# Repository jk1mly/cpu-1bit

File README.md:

# cpu-1bit
MC14500 1bit CPU

MC14500Bを使って実験を行うための基板と、プログラムをEPROMの代わりにPICに入れるソフト
MC14500Bのソフトはprogcd.hに記述
ニーモニックどはopcode.hに定義
main.cはアドレスに従ってデータを出すのみ
PICでの遅延が大きいので16F1938を32Mで動かしている
（あくまでもMC14500Bを使うのが目的）

ICソケットに実装する前に電源のショートなど確認する
電池を入れて電源を供給、PWRのLEDで電源極性を確認
電源を切ってICを実装、向きがバラバラなので注意
J3はS；スロー側に設定、ジャンパポストはオープンで良い
IN(J10)とOUT(J4)のb1、INのb2をGND(J6 3)、b3を+V(J6 1)に接続
（テスト用のプログラムだけならb3のみで良い、接続はプログラムに依存）
電源を入れて異常がなければPICkitを接続
（PICkitからは電源を供給しない・デフォルト）
PICにプログラムしたらPICkitを外す
RUNのスイッチを押すとプルグラムが動く

（PICで動かすなら3Vか4.5V）
SW4を押すとCPUがリセットされる
同時にROMアドレスの上位が1になりEPROMの書き込んでない領域になる
これによりCPUにはFが入力されるのでFLGFが出てぷrグラムカウンタが0になる
試験用のプログラムはDIPスイッチのNOT, AND, OR, XORをLEDに表示する

改善点
SW4とパラに0.1uFを入れておいた方が良い
（電源ON時にリセット状態で止められる・動かしたいならSW3）
RUNとWRITEのLEDを付けておいた方が良い
データとして0,1、ラッチしたデータを読める入力があった方が良い
（ジャンパするよう基板を作ってあるが、ジャンパポストを設けるべき）
ラッチ4ビットのLEDに入れる抵抗は別回路な方が良い
（外部I/Oで使うための抵抗と兼用になっている）

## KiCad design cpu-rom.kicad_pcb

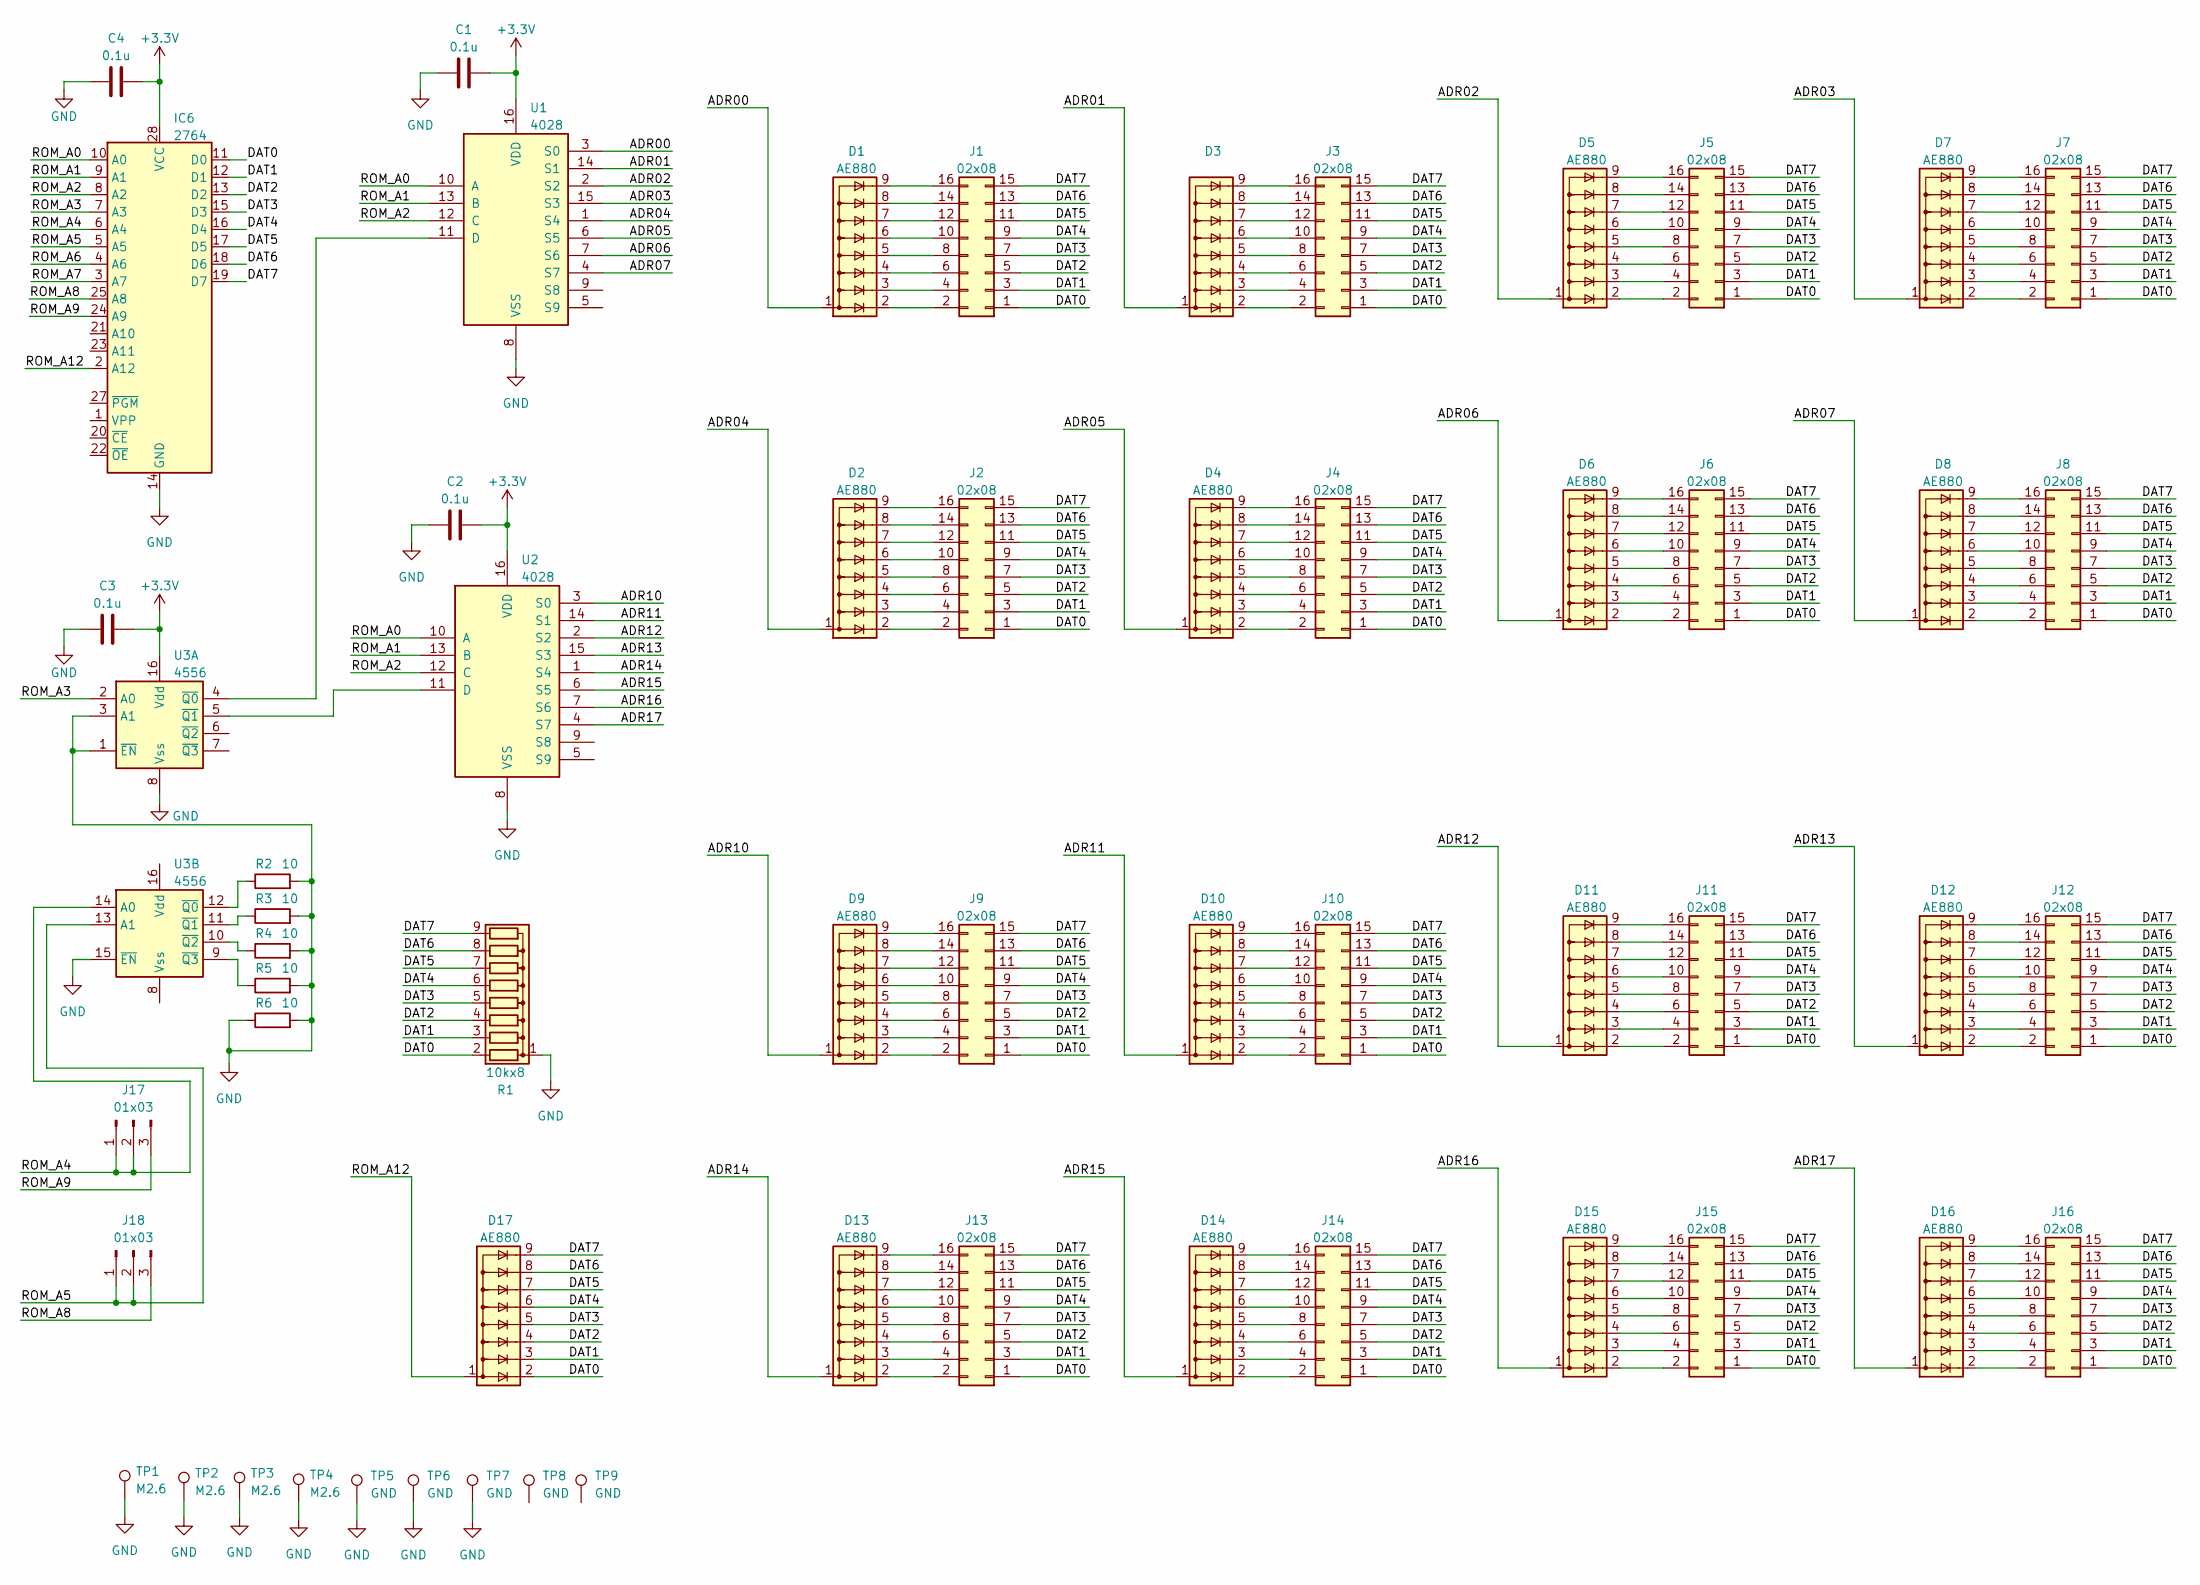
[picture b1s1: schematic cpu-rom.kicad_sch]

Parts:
C1, C2, C3, C4: 0.1u; C_Disc_P2.54mm
D1, D2, D3, D4, D5, D6, D7, D8, D9, D10, D11, D12, D13, D14, D15, D16, D17: AE880; R_Array_SIP9
IC6: 2764; DIP-28_W15.24mm_Socket_mini
J1, J2, J3, J4, J5, J6, J7, J8, J9, J10, J11, J12, J13, J14, J15, J16: 02x08; PinHeader_2x08_P2.54mm_Vertical
J17, J18: 01x03; PinHeader_1x03_P2.54mm_Vertical
R1: 10kx8; R_Array_SIP9
R2, R3, R4, R5, R6: 10; R_Axial_DIN0207_L6.3mm_D2.2mm_P2.54mm_Vertical
TP1, TP2, TP3, TP4: M2.6; TestPoint_Drill3mm
TP5, TP6, TP7, TP8, TP9: GND; TestPoint_2Pads_Pitch2.54mm_Drill0.8mm
U1, U2: 4028; DIP-16_W7.62mm_Socket_mini
U3: 4556; DIP-16_W7.62mm_Socket_mini

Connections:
+3.3V: C1.2, C2.2, C3.2, C4.2, IC6.28 (VCC), U1.16 (VDD), U2.16 (VDD), U3.16 (Vdd)
/ADR00: D1.1 (common), U1.3 (S0)
/ADR01: D3.1 (common), U1.14 (S1)
/ADR02: D5.1 (common), U1.2 (S2)
/ADR03: D7.1 (common), U1.15 (S3)
/ADR04: D2.1 (common), U1.1 (S4)
/ADR05: D4.1 (common), U1.6 (S5)
/ADR06: D6.1 (common), U1.7 (S6)
/ADR07: D8.1 (common), U1.4 (S7)
/ADR10: D9.1 (common), U2.3 (S0)
/ADR11: D10.1 (common), U2.14 (S1)
/ADR12: D11.1 (common), U2.2 (S2)
/ADR13: D12.1 (common), U2.15 (S3)
/ADR14: D13.1 (common), U2.1 (S4)
/ADR15: D14.1 (common), U2.6 (S5)
/ADR16: D15.1 (common), U2.7 (S6)
/ADR17: D16.1 (common), U2.4 (S7)
/DAT0: D17.2 (R1), IC6.11 (D0), J1.1, J2.1, J3.1, J4.1, J5.1, J6.1, J7.1, J8.1, J9.1, J10.1, J11.1, J12.1, J13.1, J14.1, J15.1, J16.1, R1.2 (R1)
/DAT1: D17.3 (R2), IC6.12 (D1), J1.3, J2.3, J3.3, J4.3, J5.3, J6.3, J7.3, J8.3, J9.3, J10.3, J11.3, J12.3, J13.3, J14.3, J15.3, J16.3, R1.3 (R2)
/DAT2: D17.4 (R3), IC6.13 (D2), J1.5, J2.5, J3.5, J4.5, J5.5, J6.5, J7.5, J8.5, J9.5, J10.5, J11.5, J12.5, J13.5, J14.5, J15.5, J16.5, R1.4 (R3)
/DAT3: D17.5 (R4), IC6.15 (D3), J1.7, J2.7, J3.7, J4.7, J5.7, J6.7, J7.7, J8.7, J9.7, J10.7, J11.7, J12.7, J13.7, J14.7, J15.7, J16.7, R1.5 (R4)
/DAT4: D17.6 (R5), IC6.16 (D4), J1.9, J2.9, J3.9, J4.9, J5.9, J6.9, J7.9, J8.9, J9.9, J10.9, J11.9, J12.9, J13.9, J14.9, J15.9, J16.9, R1.6 (R5)
/DAT5: D17.7 (R6), IC6.17 (D5), J1.11, J2.11, J3.11, J4.11, J5.11, J6.11, J7.11, J8.11, J9.11, J10.11, J11.11, J12.11, J13.11, J14.11, J15.11, J16.11, R1.7 (R6)
/DAT6: D17.8 (R7), IC6.18 (D6), J1.13, J2.13, J3.13, J4.13, J5.13, J6.13, J7.13, J8.13, J9.13, J10.13, J11.13, J12.13, J13.13, J14.13, J15.13, J16.13, R1.8 (R7)
/DAT7: D17.9 (R8), IC6.19 (D7), J1.15, J2.15, J3.15, J4.15, J5.15, J6.15, J7.15, J8.15, J9.15, J10.15, J11.15, J12.15, J13.15, J14.15, J15.15, J16.15, R1.9 (R8)
/ROM_A0: IC6.10 (A0), U1.10 (A), U2.10 (A)
/ROM_A1: IC6.9 (A1), U1.13 (B), U2.13 (B)
/ROM_A2: IC6.8 (A2), U1.12 (C), U2.12 (C)
/ROM_A3: IC6.7 (A3), U3.2 (A0)
/ROM_A4: IC6.6 (A4), J17.1, J17.2, U3.14 (A0)
/ROM_A5: IC6.5 (A5), J18.1, J18.2, U3.13 (A1)
/ROM_A6: IC6.4 (A6)
/ROM_A7: IC6.3 (A7)
/ROM_A8: IC6.25 (A8), J18.3
/ROM_A9: IC6.24 (A9), J17.3
/ROM_A12: D17.1 (common), IC6.2 (A12)
GND: C1.1, C2.1, C3.1, C4.1, IC6.14 (GND), R1.1 (common), R2.2, R3.2, R4.2, R5.2, R6.1, R6.2, TP1.1, TP2.1, TP3.1, TP4.1, TP5.1, TP6.1, TP7.1, U1.8 (VSS), U2.8 (VSS), U3.1 (~EN), U3.3 (A1), U3.8 (Vss), U3.15 (~EN)
unnamed: D1.2 (R1), J1.2
unnamed: D1.3 (R2), J1.4
unnamed: D1.4 (R3), J1.6
unnamed: D1.5 (R4), J1.8
unnamed: D1.6 (R5), J1.10
unnamed: D1.7 (R6), J1.12
unnamed: D1.8 (R7), J1.14
unnamed: D1.9 (R8), J1.16
unnamed: D2.2 (R1), J2.2
unnamed: D2.3 (R2), J2.4
unnamed: D2.4 (R3), J2.6
unnamed: D2.5 (R4), J2.8
unnamed: D2.6 (R5), J2.10
unnamed: D2.7 (R6), J2.12
unnamed: D2.8 (R7), J2.14
unnamed: D2.9 (R8), J2.16
unnamed: D3.2 (R1), J3.2
unnamed: D3.3 (R2), J3.4
unnamed: D3.4 (R3), J3.6
unnamed: D3.5 (R4), J3.8
unnamed: D3.6 (R5), J3.10
unnamed: D3.7 (R6), J3.12
unnamed: D3.8 (R7), J3.14
unnamed: D3.9 (R8), J3.16
unnamed: D4.2 (R1), J4.2
unnamed: D4.3 (R2), J4.4
unnamed: D4.4 (R3), J4.6
unnamed: D4.5 (R4), J4.8
unnamed: D4.6 (R5), J4.10
unnamed: D4.7 (R6), J4.12
unnamed: D4.8 (R7), J4.14
unnamed: D4.9 (R8), J4.16
unnamed: D5.2 (R1), J5.2
unnamed: D5.3 (R2), J5.4
unnamed: D5.4 (R3), J5.6
unnamed: D5.5 (R4), J5.8
unnamed: D5.6 (R5), J5.10
unnamed: D5.7 (R6), J5.12
unnamed: D5.8 (R7), J5.14
unnamed: D5.9 (R8), J5.16
unnamed: D6.2 (R1), J6.2
unnamed: D6.3 (R2), J6.4
unnamed: D6.4 (R3), J6.6
unnamed: D6.5 (R4), J6.8
unnamed: D6.6 (R5), J6.10
unnamed: D6.7 (R6), J6.12
unnamed: D6.8 (R7), J6.14
unnamed: D6.9 (R8), J6.16
unnamed: D7.2 (R1), J7.2
unnamed: D7.3 (R2), J7.4
unnamed: D7.4 (R3), J7.6
unnamed: D7.5 (R4), J7.8
unnamed: D7.6 (R5), J7.10
unnamed: D7.7 (R6), J7.12
unnamed: D7.8 (R7), J7.14
unnamed: D7.9 (R8), J7.16
unnamed: D8.2 (R1), J8.2
unnamed: D8.3 (R2), J8.4
unnamed: D8.4 (R3), J8.6
unnamed: D8.5 (R4), J8.8
unnamed: D8.6 (R5), J8.10
unnamed: D8.7 (R6), J8.12
unnamed: D8.8 (R7), J8.14
unnamed: D8.9 (R8), J8.16
unnamed: D9.2 (R1), J9.2
unnamed: D9.3 (R2), J9.4
unnamed: D9.4 (R3), J9.6
unnamed: D9.5 (R4), J9.8
unnamed: D9.6 (R5), J9.10
unnamed: D9.7 (R6), J9.12
unnamed: D9.8 (R7), J9.14
unnamed: D9.9 (R8), J9.16
unnamed: D10.2 (R1), J10.2
unnamed: D10.3 (R2), J10.4
unnamed: D10.4 (R3), J10.6
unnamed: D10.5 (R4), J10.8
unnamed: D10.6 (R5), J10.10
unnamed: D10.7 (R6), J10.12
unnamed: D10.8 (R7), J10.14
unnamed: D10.9 (R8), J10.16
unnamed: D11.2 (R1), J11.2
unnamed: D11.3 (R2), J11.4
unnamed: D11.4 (R3), J11.6
unnamed: D11.5 (R4), J11.8
unnamed: D11.6 (R5), J11.10
unnamed: D11.7 (R6), J11.12
unnamed: D11.8 (R7), J11.14
unnamed: D11.9 (R8), J11.16
unnamed: D12.2 (R1), J12.2
unnamed: D12.3 (R2), J12.4
unnamed: D12.4 (R3), J12.6
unnamed: D12.5 (R4), J12.8
unnamed: D12.6 (R5), J12.10
unnamed: D12.7 (R6), J12.12
unnamed: D12.8 (R7), J12.14
unnamed: D12.9 (R8), J12.16
unnamed: D13.2 (R1), J13.2
unnamed: D13.3 (R2), J13.4
unnamed: D13.4 (R3), J13.6
unnamed: D13.5 (R4), J13.8
unnamed: D13.6 (R5), J13.10
unnamed: D13.7 (R6), J13.12
unnamed: D13.8 (R7), J13.14
unnamed: D13.9 (R8), J13.16
unnamed: D14.2 (R1), J14.2
unnamed: D14.3 (R2), J14.4
unnamed: D14.4 (R3), J14.6
unnamed: D14.5 (R4), J14.8
unnamed: D14.6 (R5), J14.10
unnamed: D14.7 (R6), J14.12
unnamed: D14.8 (R7), J14.14
unnamed: D14.9 (R8), J14.16
unnamed: D15.2 (R1), J15.2
unnamed: D15.3 (R2), J15.4
unnamed: D15.4 (R3), J15.6
unnamed: D15.5 (R4), J15.8
unnamed: D15.6 (R5), J15.10
unnamed: D15.7 (R6), J15.12
unnamed: D15.8 (R7), J15.14
unnamed: D15.9 (R8), J15.16
unnamed: D16.2 (R1), J16.2
unnamed: D16.3 (R2), J16.4
unnamed: D16.4 (R3), J16.6
unnamed: D16.5 (R4), J16.8
unnamed: D16.6 (R5), J16.10
unnamed: D16.7 (R6), J16.12
unnamed: D16.8 (R7), J16.14
unnamed: D16.9 (R8), J16.16
unnamed: U1.11 (D), U3.4 (~Q0)
unnamed: U2.11 (D), U3.5 (~Q1)
unnamed: R2.1, U3.12 (~Q0)
unnamed: R3.1, U3.11 (~Q1)
unnamed: R4.1, U3.10 (~Q2)
unnamed: R5.1, U3.9 (~Q3)

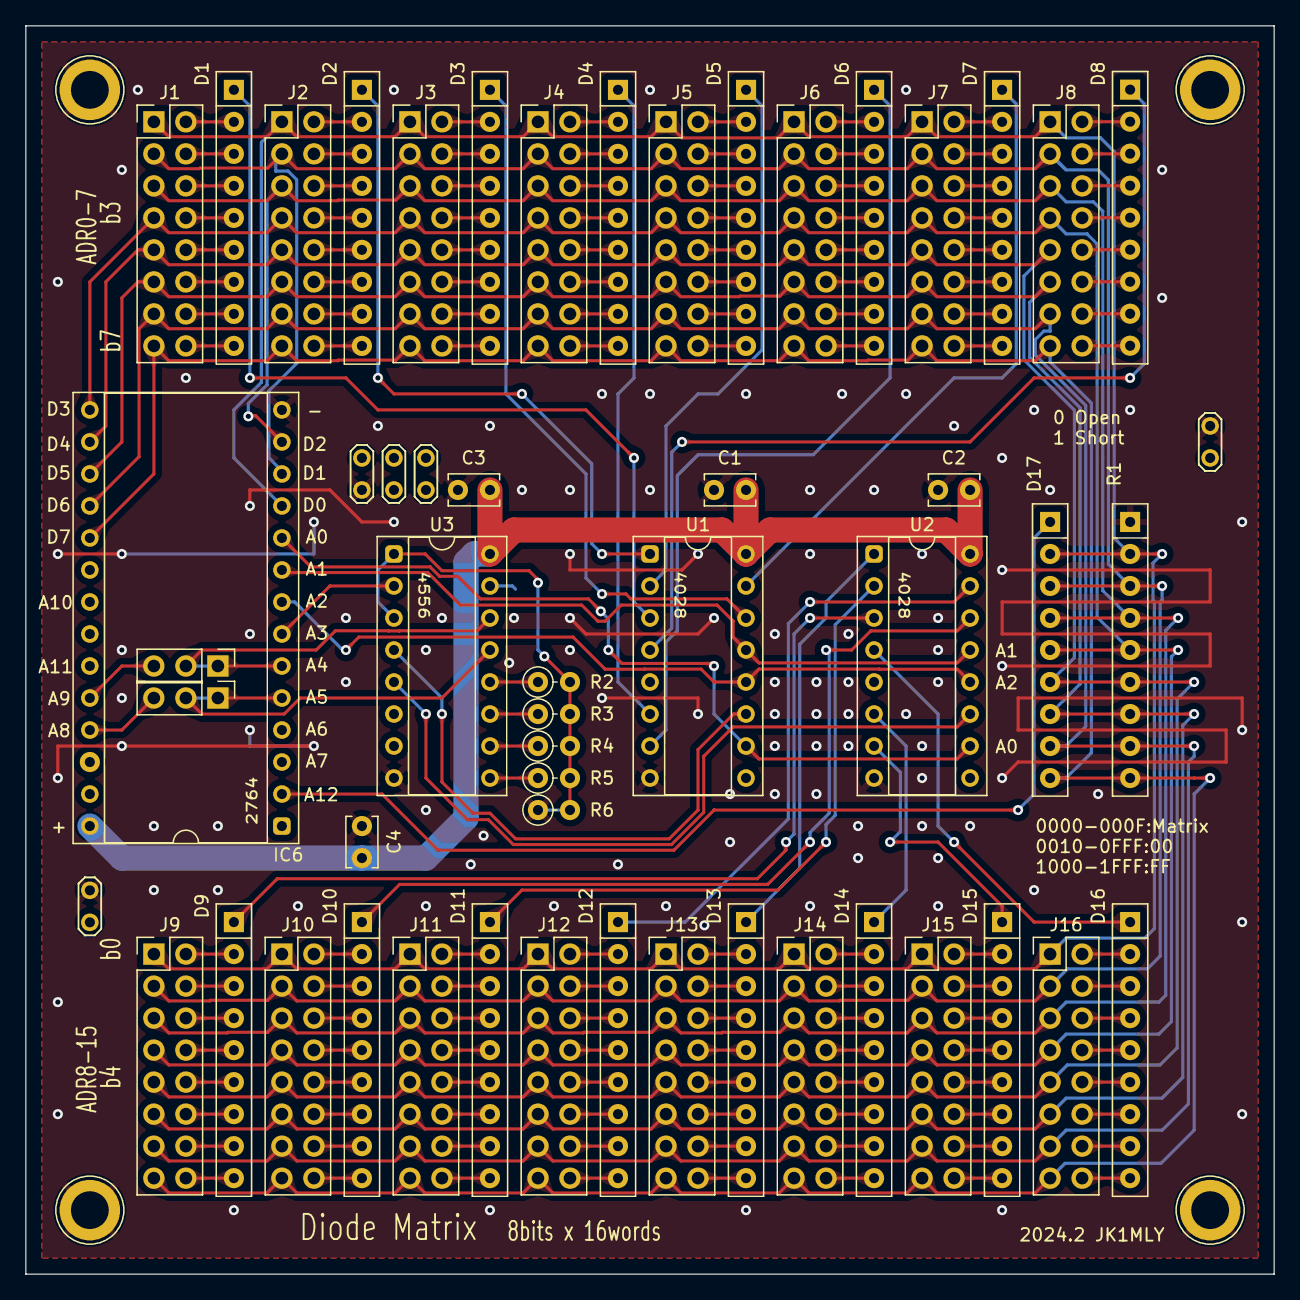
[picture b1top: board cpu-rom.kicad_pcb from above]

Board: 2 copper layers, 99.1 x 99.1 mm, 58 parts (0 on the bottom side), 169 nets.

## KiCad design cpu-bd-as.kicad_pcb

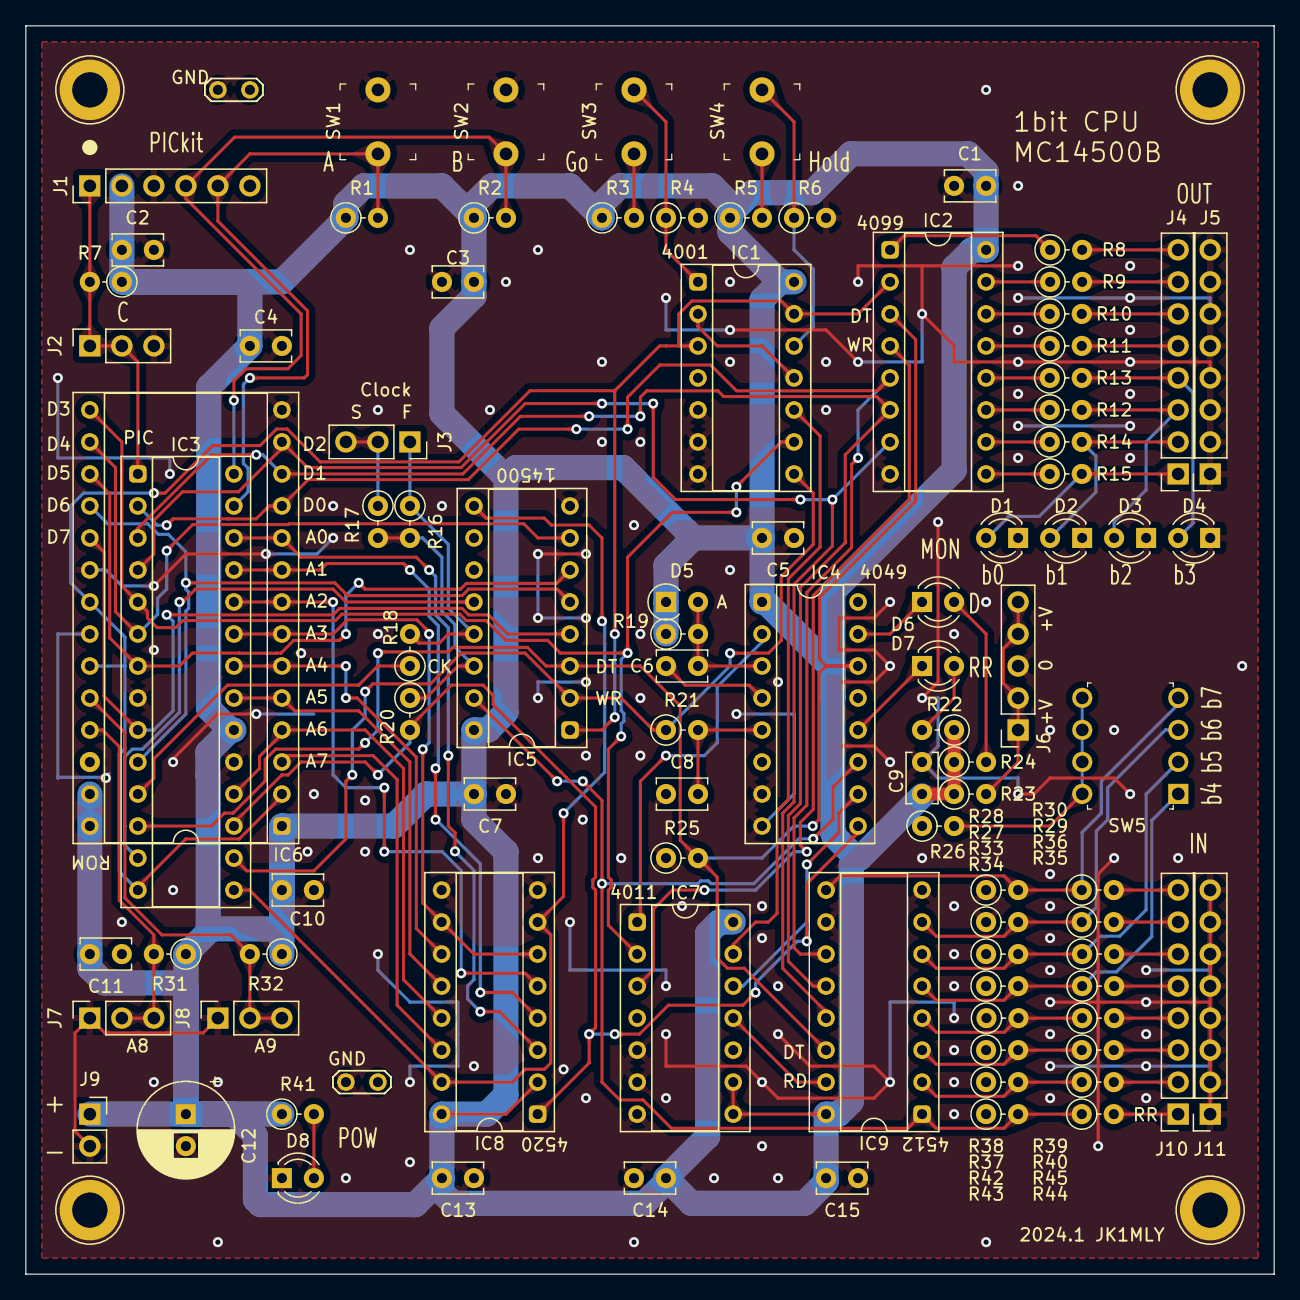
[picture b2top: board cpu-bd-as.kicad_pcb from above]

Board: 2 copper layers, 99.1 x 99.1 mm, 99 parts (0 on the bottom side), 85 nets.

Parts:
C1, C2, C3, C4, C5, C7, C9, C10, C11, C13, C14, C15: 0.1u; C_Disc_P2.54mm
C6, C8: 1000p; C_Disc_P2.54mm
C12: 10u; CP_Radial_D7.5mm_P2.54mm
D1, D2, D3, D4, D6, D7, D8: LED; LED_D3.0mm
D5: D; D_A-405_P2.54mm_Vertical_AnodeUp
IC1: 4001; DIP-14_W7.62mm_Socket_mini
IC2: 4099; DIP-16_W7.62mm_Socket_mini
IC3: PIC16F1938; DIP-28_W7.62mm_Socket_mini
IC4: 4049; DIP-16_W7.62mm_Socket_mini
IC5: MC14500B; DIP-16_W7.62mm_Socket_mini
IC6: 2764; DIP-28_W15.24mm_Socket_mini
IC7: 4011; DIP-14_W7.62mm_Socket_mini
IC8: 4520; DIP-16_W7.62mm_Socket_mini
IC9: 4512; DIP-16_W7.62mm_Socket_mini
J1: Conn_06; PinHeader_1x06_P2.54mm_Vertical
J2, J3, J7, J8: Conn_01x03_Pin; PinSocket_1x03_P2.54mm_Vertical
J4, J5, J10, J11: Conn_08; PinSocket_1x08_P2.54mm_Vertical
J6: Conn_01x05_Pin; PinSocket_1x05_P2.54mm_Vertical
J9: Conn_02; PinSocket_1x02_P2.54mm_Vertical
R1, R2, R4, R6, R7, R19, R31, R32: 10k; R_Axial_DIN0207_L6.3mm_D2.2mm_P2.54mm_Vertical
R3, R5, R8, R9, R10, R11, R12, R13, R14, R15, R23, R26, R29, R30, R35, R36, R39, R40, R44, R45: 100; R_Axial_DIN0207_L6.3mm_D2.2mm_P2.54mm_Vertical
R16: 1M; R_Axial_DIN0207_L6.3mm_D2.2mm_P2.54mm_Vertical
R17: 47k; R_Axial_DIN0207_L6.3mm_D2.2mm_P2.54mm_Vertical
R18: 1k; R_Axial_DIN0207_L6.3mm_D2.2mm_P2.54mm_Vertical
R20: 22; R_Axial_DIN0207_L6.3mm_D2.2mm_P2.54mm_Vertical
R21: 220; R_Axial_DIN0207_L6.3mm_D2.2mm_P2.54mm_Vertical
R22, R24, R41: 470; R_Axial_DIN0207_L6.3mm_D2.2mm_P2.54mm_Vertical
R25, R27, R28, R33, R34, R37, R38, R42, R43: 100k; R_Axial_DIN0207_L6.3mm_D2.2mm_P2.54mm_Vertical
SW1, SW2, SW3, SW4: SW_Push; Switch_2P
SW5: SW_DIP_x04; DIP-8_W7.62mm
TP1, TP2, TP3, TP4: M2.6; TestPoint_Loop_D3.80mm_Drill2.8mm
TP5, TP6: GND; TestPoint_2Pads_Pitch2.54mm_Drill0.8mm

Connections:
+3.3V: C1.2, C2.1, C3.1, C4.2, C5.2, C7.2, C9.1, C10.1, C11.2, C12.1, C13.2, C14.1, C15.2, D5.1 (K), IC1.14 (VDD), IC2.16 (Vdd), IC3.20 (VDD), IC4.1 (VCC), IC5.16 (VCC), IC6.1 (VPP), IC6.27 (~PGM), IC6.28 (VCC), IC7.8, IC7.9, IC7.14 (VDD), IC8.2 (Enable), IC8.16 (VDD), IC9.16 (Vdd), J1.2, J9.1, R1.1, R2.1, R3.1, R5.1, R7.1, R19.1, R22.1, R23.1, R24.1, R26.1, R31.1, R32.1, R41.1
/CLK: IC3.17 (RC6), IC4.9, IC8.1 (CK), R20.2
/DATA: IC2.3 (D), IC3.12 (RC1), IC4.14, IC5.3 (DATA), IC9.14 (Q), R25.2
/FLGF: IC3.15 (RC4), IC5.9 (FLGF), IC8.7 (Reset), IC8.15 (Reset)
/GO: IC1.1, R4.1, SW3.2
/HALT: IC1.12, R6.1, SW4.2
/JMP: IC3.13 (RC2), IC5.12 (JMP)
/L_b0: D1.2 (A), J4.1, R15.2
/L_b1: D2.2 (A), J4.2, R14.2
/L_b2: D3.2 (A), J4.3, R12.2
/L_b3: D4.2 (A), J4.4, R13.2
/ROM_A0: IC3.26 (RB5), IC6.10 (A0), IC8.3 (Q1)
/ROM_A1: IC3.25 (RB4), IC6.9 (A1), IC8.4 (Q2)
/ROM_A2: IC3.24 (RB3), IC6.8 (A2), IC8.5 (Q3)
/ROM_A3: IC3.23 (RB2), IC6.7 (A3), IC8.6 (Q4), IC8.10 (Enable)
/ROM_A4: IC3.22 (RB1), IC6.6 (A4), IC8.11 (Q1)
/ROM_A5: IC3.21 (RB0), IC6.5 (A5), IC8.12 (Q2)
/ROM_A6: IC3.18 (RC7), IC6.4 (A6), IC8.13 (Q3)
/ROM_A7: IC6.3 (A7), IC8.14 (Q4)
/ROM_D0: IC2.5 (A0), IC3.2 (RA0), IC6.11 (D0), IC9.11 (S0)
/ROM_D1: IC2.6 (A1), IC3.3 (RA1), IC6.12 (D1), IC9.12 (S1)
/ROM_D2: IC2.7 (A2), IC3.4 (RA2), IC6.13 (D2), IC9.13 (S2)
/ROM_D3: IC1.9, IC3.5 (RA3), IC6.15 (D3), IC7.2
/ROM_D4: IC3.6 (RA4), IC5.7 (I0), IC6.16 (D4)
/ROM_D5: IC3.7 (RA5), IC5.6 (I1), IC6.17 (D5)
/ROM_D6: IC3.10 (RA6), IC5.5 (I2), IC6.18 (D6)
/ROM_D7: IC3.9 (RA7), IC5.4 (I3), IC6.19 (D7)
/RR: IC4.11, IC5.15 (RR), IC9.1 (I0), R43.2, R44.1
/RST: IC1.3, IC1.13, IC2.2 (R), IC3.14 (RC3), IC5.1 (RST), IC6.2 (A12), IC6.21 (A10), IC6.23 (A11)
/S_b4: IC9.5 (I4), R34.2, R35.1, SW5.1
/S_b5: IC9.6 (I5), R33.2, R36.1, SW5.2
/S_b6: IC9.7 (I6), R27.2, R29.1, SW5.3
/S_b7: IC9.9 (I7), R28.2, R30.1, SW5.4
/WRITE: IC1.8, IC3.16 (RC5), IC5.2 (WRITE), R21.1
/X2: IC5.13 (X2), J3.1, R16.1, R18.2
/nCS_I0: IC7.11, IC9.15 (~EN)
/nCS_O0: IC2.4 (WR), IC7.3
/nWR_PLS: IC4.2, IC7.1
GND: C1.1, C2.2, C3.2, C4.1, C5.1, C7.1, C8.2, C9.2, C10.2, C12.2, C13.1, C14.2, C15.1, D1.1 (K), D2.1 (K), D3.1 (K), D4.1 (K), D8.1 (K), IC1.5, IC1.6, IC1.7 (VSS), IC2.8 (Vss), IC3.8 (VSS), IC3.19 (VSS), IC4.7, IC4.8 (VSS), IC5.8 (GND), IC6.14 (GND), IC6.20 (~CE), IC6.22 (~OE), IC7.5, IC7.6, IC7.7 (VSS), IC8.8 (VSS), IC8.9 (CK), IC9.8 (Vss), IC9.10 (~E), J1.3, J2.3, J5.1, J5.2, J5.3, J5.4, J5.5, J5.6, J5.7, J5.8, J6.3, J7.1, J8.1, J9.2, J11.1, J11.2, J11.3, J11.4, J11.5, J11.6, J11.7, J11.8, R4.2, R6.2, R25.1, R27.1, R28.1, R33.1, R34.1, R37.1, R38.1, R42.1, R43.1, SW1.2, SW2.2, TP1.1, TP2.1, TP3.1, TP4.1, TP5.1, TP6.1
unnamed: C6.1, IC4.4
unnamed: C8.1, IC4.5, R21.2
unnamed: C6.2, D5.2 (A), IC4.3, R19.2
unnamed: D6.2 (A), R24.2
unnamed: D6.1 (K), IC4.15
unnamed: D7.2 (A), R22.2
unnamed: D7.1 (K), IC4.12
unnamed: D8.2 (A), R41.2
unnamed: IC1.10, IC7.13
unnamed: IC1.2, IC1.11
unnamed: IC2.9 (Q0), R15.1
unnamed: IC2.10 (Q1), R14.1
unnamed: IC2.11 (Q2), R12.1
unnamed: IC2.12 (Q3), R13.1
unnamed: IC2.13 (Q4), R11.1
unnamed: IC2.14 (Q5), R10.1
unnamed: IC2.15 (Q6), R9.1
unnamed: IC2.1 (Q7), R8.1
unnamed: IC3.27 (RB6/ICSPCLK), J1.5, R1.2, SW1.1
unnamed: IC3.28 (RB7/ICSPDAT), J1.4, R2.2, SW2.1
unnamed: IC3.11 (RC0), R18.1
unnamed: IC3.1 (RE3/MCLR), J1.1, J2.1, J2.2, R7.2
unnamed: IC4.10, IC7.12
unnamed: IC5.14 (X1), R16.2, R17.2, R20.1
unnamed: IC6.25 (A8), J7.2, J7.3, R31.2
unnamed: IC6.24 (A9), J8.2, J8.3, R32.2
unnamed: IC9.2 (I1), R42.2, R45.1
unnamed: IC9.3 (I2), R37.2, R40.1
unnamed: IC9.4 (I3), R38.2, R39.1
unnamed: J3.2, J3.3, R17.1
unnamed: J4.5, R11.2
unnamed: J4.6, R10.2
unnamed: J4.7, R9.2
unnamed: J4.8, R8.2
unnamed: J6.1, J6.2, J6.4, J6.5, R23.2
unnamed: J10.1, R44.2
unnamed: J10.2, R45.2
unnamed: J10.3, R40.2
unnamed: J10.4, R39.2
unnamed: J10.5, R35.2
unnamed: J10.6, R36.2
unnamed: J10.7, R29.2
unnamed: J10.8, R30.2
unnamed: R3.2, SW3.1
unnamed: R5.2, SW4.1
unnamed: R26.2, SW5.5, SW5.6, SW5.7, SW5.8

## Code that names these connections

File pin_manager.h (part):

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// get/set IO_RA0 aliases
#define IO_RA0_TRIS                 TRISAbits.TRISA0
#define IO_RA0_LAT                  LATAbits.LATA0
#define IO_RA0_PORT                 PORTAbits.RA0
#define IO_RA0_ANS                  ANSELAbits.ANSA0
#define IO_RA0_SetHigh()            do { LATAbits.LATA0 = 1; } while(0)
#define IO_RA0_SetLow()             do { LATAbits.LATA0 = 0; } while(0)
#define IO_RA0_Toggle()             do { LATAbits.LATA0 = ~LATAbits.LATA0; } while(0)
#define IO_RA0_GetValue()           PORTAbits.RA0
#define IO_RA0_SetDigitalInput()    do { TRISAbits.TRISA0 = 1; } while(0)
#define IO_RA0_SetDigitalOutput()   do { TRISAbits.TRISA0 = 0; } while(0)
#define IO_RA0_SetAnalogMode()      do { ANSELAbits.ANSA0 = 1; } while(0)
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// get/set IO_RA1 aliases
#define IO_RA1_TRIS                 TRISAbits.TRISA1
#define IO_RA1_LAT                  LATAbits.LATA1
#define IO_RA1_PORT                 PORTAbits.RA1
#define IO_RA1_ANS                  ANSELAbits.ANSA1
#define IO_RA1_SetHigh()            do { LATAbits.LATA1 = 1; } while(0)
#define IO_RA1_SetLow()             do { LATAbits.LATA1 = 0; } while(0)
#define IO_RA1_Toggle()             do { LATAbits.LATA1 = ~LATAbits.LATA1; } while(0)
#define IO_RA1_GetValue()           PORTAbits.RA1
#define IO_RA1_SetDigitalInput()    do { TRISAbits.TRISA1 = 1; } while(0)
#define IO_RA1_SetDigitalOutput()   do { TRISAbits.TRISA1 = 0; } while(0)
#define IO_RA1_SetAnalogMode()      do { ANSELAbits.ANSA1 = 1; } while(0)
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// get/set IO_RA2 aliases
#define IO_RA2_TRIS                 TRISAbits.TRISA2
#define IO_RA2_LAT                  LATAbits.LATA2
#define IO_RA2_PORT                 PORTAbits.RA2
#define IO_RA2_ANS                  ANSELAbits.ANSA2
#define IO_RA2_SetHigh()            do { LATAbits.LATA2 = 1; } while(0)
#define IO_RA2_SetLow()             do { LATAbits.LATA2 = 0; } while(0)
#define IO_RA2_Toggle()             do { LATAbits.LATA2 = ~LATAbits.LATA2; } while(0)
#define IO_RA2_GetValue()           PORTAbits.RA2
#define IO_RA2_SetDigitalInput()    do { TRISAbits.TRISA2 = 1; } while(0)
#define IO_RA2_SetDigitalOutput()   do { TRISAbits.TRISA2 = 0; } while(0)
#define IO_RA2_SetAnalogMode()      do { ANSELAbits.ANSA2 = 1; } while(0)
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// get/set IO_RA3 aliases
#define IO_RA3_TRIS                 TRISAbits.TRISA3
#define IO_RA3_LAT                  LATAbits.LATA3
#define IO_RA3_PORT                 PORTAbits.RA3
#define IO_RA3_ANS                  ANSELAbits.ANSA3
#define IO_RA3_SetHigh()            do { LATAbits.LATA3 = 1; } while(0)
#define IO_RA3_SetLow()             do { LATAbits.LATA3 = 0; } while(0)
#define IO_RA3_Toggle()             do { LATAbits.LATA3 = ~LATAbits.LATA3; } while(0)
#define IO_RA3_GetValue()           PORTAbits.RA3
#define IO_RA3_SetDigitalInput()    do { TRISAbits.TRISA3 = 1; } while(0)
#define IO_RA3_SetDigitalOutput()   do { TRISAbits.TRISA3 = 0; } while(0)
#define IO_RA3_SetAnalogMode()      do { ANSELAbits.ANSA3 = 1; } while(0)
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// get/set IO_RA4 aliases
#define IO_RA4_TRIS                 TRISAbits.TRISA4
#define IO_RA4_LAT                  LATAbits.LATA4
#define IO_RA4_PORT                 PORTAbits.RA4
#define IO_RA4_ANS                  ANSELAbits.ANSA4
#define IO_RA4_SetHigh()            do { LATAbits.LATA4 = 1; } while(0)
#define IO_RA4_SetLow()             do { LATAbits.LATA4 = 0; } while(0)
#define IO_RA4_Toggle()             do { LATAbits.LATA4 = ~LATAbits.LATA4; } while(0)
#define IO_RA4_GetValue()           PORTAbits.RA4
#define IO_RA4_SetDigitalInput()    do { TRISAbits.TRISA4 = 1; } while(0)
#define IO_RA4_SetDigitalOutput()   do { TRISAbits.TRISA4 = 0; } while(0)
#define IO_RA4_SetAnalogMode()      do { ANSELAbits.ANSA4 = 1; } while(0)
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// get/set IO_RA5 aliases
#define IO_RA5_TRIS                 TRISAbits.TRISA5
#define IO_RA5_LAT                  LATAbits.LATA5
#define IO_RA5_PORT                 PORTAbits.RA5
#define IO_RA5_ANS                  ANSELAbits.ANSA5
#define IO_RA5_SetHigh()            do { LATAbits.LATA5 = 1; } while(0)
#define IO_RA5_SetLow()             do { LATAbits.LATA5 = 0; } while(0)
#define IO_RA5_Toggle()             do { LATAbits.LATA5 = ~LATAbits.LATA5; } while(0)
#define IO_RA5_GetValue()           PORTAbits.RA5
#define IO_RA5_SetDigitalInput()    do { TRISAbits.TRISA5 = 1; } while(0)
#define IO_RA5_SetDigitalOutput()   do { TRISAbits.TRISA5 = 0; } while(0)
#define IO_RA5_SetAnalogMode()      do { ANSELAbits.ANSA5 = 1; } while(0)
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// get/set IO_RA6 aliases
#define IO_RA6_TRIS                 TRISAbits.TRISA6
#define IO_RA6_LAT                  LATAbits.LATA6
#define IO_RA6_PORT                 PORTAbits.RA6
#define IO_RA6_SetHigh()            do { LATAbits.LATA6 = 1; } while(0)
#define IO_RA6_SetLow()             do { LATAbits.LATA6 = 0; } while(0)
#define IO_RA6_Toggle()             do { LATAbits.LATA6 = ~LATAbits.LATA6; } while(0)
#define IO_RA6_GetValue()           PORTAbits.RA6
#define IO_RA6_SetDigitalInput()    do { TRISAbits.TRISA6 = 1; } while(0)
#define IO_RA6_SetDigitalOutput()   do { TRISAbits.TRISA6 = 0; } while(0)

// get/set IO_RA7 aliases
#define IO_RA7_TRIS                 TRISAbits.TRISA7
#define IO_RA7_LAT                  LATAbits.LATA7
#define IO_RA7_PORT                 PORTAbits.RA7
#define IO_RA7_SetHigh()            do { LATAbits.LATA7 = 1; } while(0)
#define IO_RA7_SetLow()             do { LATAbits.LATA7 = 0; } while(0)
#define IO_RA7_Toggle()             do { LATAbits.LATA7 = ~LATAbits.LATA7; } while(0)
#define IO_RA7_GetValue()           PORTAbits.RA7
#define IO_RA7_SetDigitalInput()    do { TRISAbits.TRISA7 = 1; } while(0)
#define IO_RA7_SetDigitalOutput()   do { TRISAbits.TRISA7 = 0; } while(0)

// get/set IO_RB0 aliases
#define IO_RB0_TRIS                 TRISBbits.TRISB0
#define IO_RB0_LAT                  LATBbits.LATB0
#define IO_RB0_PORT                 PORTBbits.RB0
#define IO_RB0_WPU                  WPUBbits.WPUB0
#define IO_RB0_ANS                  ANSELBbits.ANSB0
#define IO_RB0_SetHigh()            do { LATBbits.LATB0 = 1; } while(0)
#define IO_RB0_SetLow()             do { LATBbits.LATB0 = 0; } while(0)
#define IO_RB0_Toggle()             do { LATBbits.LATB0 = ~LATBbits.LATB0; } while(0)
#define IO_RB0_GetValue()           PORTBbits.RB0
#define IO_RB0_SetDigitalInput()    do { TRISBbits.TRISB0 = 1; } while(0)
#define IO_RB0_SetDigitalOutput()   do { TRISBbits.TRISB0 = 0; } while(0)
#define IO_RB0_SetPullup()          do { WPUBbits.WPUB0 = 1; } while(0)
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// get/set IO_RB1 aliases
#define IO_RB1_TRIS                 TRISBbits.TRISB1
#define IO_RB1_LAT                  LATBbits.LATB1
#define IO_RB1_PORT                 PORTBbits.RB1
#define IO_RB1_WPU                  WPUBbits.WPUB1
#define IO_RB1_ANS                  ANSELBbits.ANSB1
#define IO_RB1_SetHigh()            do { LATBbits.LATB1 = 1; } while(0)
#define IO_RB1_SetLow()             do { LATBbits.LATB1 = 0; } while(0)
#define IO_RB1_Toggle()             do { LATBbits.LATB1 = ~LATBbits.LATB1; } while(0)
#define IO_RB1_GetValue()           PORTBbits.RB1
#define IO_RB1_SetDigitalInput()    do { TRISBbits.TRISB1 = 1; } while(0)
#define IO_RB1_SetDigitalOutput()   do { TRISBbits.TRISB1 = 0; } while(0)
#define IO_RB1_SetPullup()          do { WPUBbits.WPUB1 = 1; } while(0)
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// get/set IO_RB2 aliases
#define IO_RB2_TRIS                 TRISBbits.TRISB2
#define IO_RB2_LAT                  LATBbits.LATB2
#define IO_RB2_PORT                 PORTBbits.RB2
#define IO_RB2_WPU                  WPUBbits.WPUB2
#define IO_RB2_ANS                  ANSELBbits.ANSB2
#define IO_RB2_SetHigh()            do { LATBbits.LATB2 = 1; } while(0)
#define IO_RB2_SetLow()             do { LATBbits.LATB2 = 0; } while(0)
#define IO_RB2_Toggle()             do { LATBbits.LATB2 = ~LATBbits.LATB2; } while(0)
#define IO_RB2_GetValue()           PORTBbits.RB2
#define IO_RB2_SetDigitalInput()    do { TRISBbits.TRISB2 = 1; } while(0)
#define IO_RB2_SetDigitalOutput()   do { TRISBbits.TRISB2 = 0; } while(0)
#define IO_RB2_SetPullup()          do { WPUBbits.WPUB2 = 1; } while(0)
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// get/set IO_RB3 aliases
#define IO_RB3_TRIS                 TRISBbits.TRISB3
#define IO_RB3_LAT                  LATBbits.LATB3
#define IO_RB3_PORT                 PORTBbits.RB3
#define IO_RB3_WPU                  WPUBbits.WPUB3
#define IO_RB3_ANS                  ANSELBbits.ANSB3
#define IO_RB3_SetHigh()            do { LATBbits.LATB3 = 1; } while(0)
#define IO_RB3_SetLow()             do { LATBbits.LATB3 = 0; } while(0)
#define IO_RB3_Toggle()             do { LATBbits.LATB3 = ~LATBbits.LATB3; } while(0)
#define IO_RB3_GetValue()           PORTBbits.RB3
#define IO_RB3_SetDigitalInput()    do { TRISBbits.TRISB3 = 1; } while(0)
#define IO_RB3_SetDigitalOutput()   do { TRISBbits.TRISB3 = 0; } while(0)
#define IO_RB3_SetPullup()          do { WPUBbits.WPUB3 = 1; } while(0)
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// get/set IO_RB4 aliases
#define IO_RB4_TRIS                 TRISBbits.TRISB4
#define IO_RB4_LAT                  LATBbits.LATB4
#define IO_RB4_PORT                 PORTBbits.RB4
#define IO_RB4_WPU                  WPUBbits.WPUB4
#define IO_RB4_ANS                  ANSELBbits.ANSB4
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

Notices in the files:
pin_manager.h:
(c) 2018 Microchip Technology Inc. and its subsidiaries.
